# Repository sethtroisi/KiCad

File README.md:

# Seth Troisi's personal KiCad projects

## HomeLightsPCB

Used in Mourning Owl and Dream Willow

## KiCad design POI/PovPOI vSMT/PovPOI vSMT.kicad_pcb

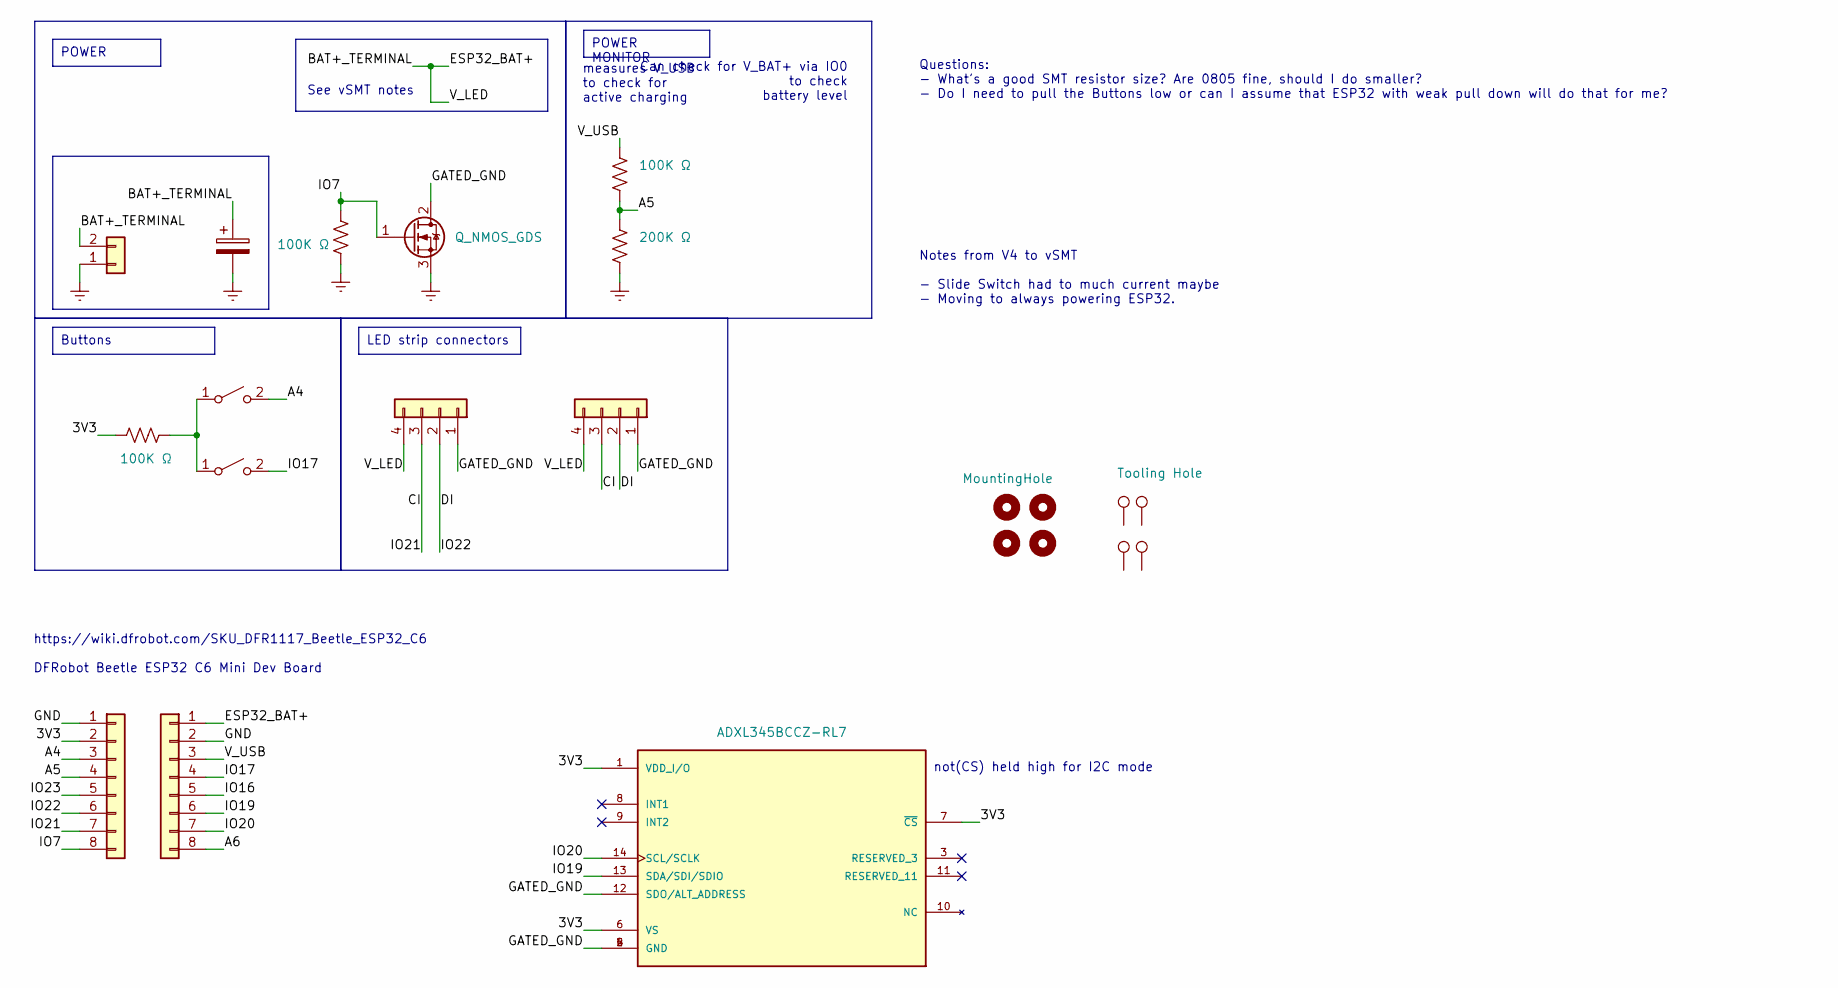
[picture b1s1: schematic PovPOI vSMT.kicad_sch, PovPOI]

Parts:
BatteryConn1: Conn_01x02; PinSocket_1x02_P2.54mm_Vertical
C2: C_Polarized; R_0805_2012Metric_Pad1.20x1.40mm_HandSolder; JLC 0805
H1, H2, H3, H4: MountingHole; MountingHole_2.2mm_M2_Pad
J2, J4: Conn_01x08; PinSocket_1x08_P2.54mm_Vertical
J3, J5: Conn_01x04; PinHeader_1x04_P2.54mm_Vertical_LARGER_HOLES
Q2: Q_NMOS_GDS; TO-252-2
R1, R5, R6: 100K Ω; R_0805_2012Metric_Pad1.20x1.40mm_HandSolder; LCSC C149504
R3: 200K Ω; R_0805_2012Metric_Pad1.20x1.40mm_HandSolder; LCSC C17539
SW1, SW2: SW_SPST; SW_SPST_EVQP7C; LCSC C388883
TP1, TP2, TP3, TP4: Tooling Hole; ToolingHole_JLCPCB
U2: ADXL345BCCZ-RL7; PQFN80P500X300X100-14N; PARTREV B; LCSC C9667

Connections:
/3V3: J2.2, R5.2, U2.1 (VDD_I/O), U2.6 (VS), U2.7 (~CS)
/A4: J2.3, SW2.2 (B)
/A5: J2.4, R1.1, R3.2
/A6: J4.8
/BAT+_TERMINAL: BatteryConn1.2, C2.1, J3.4, J4.1, J5.4
/CI: J2.7, J3.3, J5.3
/DI: J2.6, J3.2, J5.2
/GATED_GND: J3.1, J5.1, Q2.2 (D), U2.2 (GND), U2.4 (GND), U2.5 (GND), U2.12 (SDO/ALT_ADDRESS)
/IO7: J2.8, Q2.1 (G), R6.2
/IO16: J4.5
/IO17: J4.4, SW1.2 (B)
/IO19: J4.6, U2.13 (SDA/SDI/SDIO)
/IO20: J4.7, U2.14 (SCL/SCLK)
/IO23: J2.5
/V_USB: J4.3, R1.2
GND: BatteryConn1.1, C2.2, J2.1, J4.2, Q2.3 (S), R3.1, R6.1
unnamed: R5.1, SW1.1 (A), SW2.1 (A)

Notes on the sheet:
POWER
LED strip connectors
POWER MONITOR
Buttons
Notes from V4 to vSMT - Slide Switch had to much current maybe - Moving to always powering ESP32.
Can check for V_BAT+ via IO0 to check battery level
https://wiki.dfrobot.com/SKU_DFR1117_Beetle_ESP32_C6 DFRobot Beetle ESP32 C6 Mini Dev Board
Questions: - What's a good SMT resistor size? Are 0805 fine, should I do smaller? - Do I need to pull the Buttons low or can I assume that ESP32 with weak pull down will do that for me?
See vSMT notes
not(CS) held high for I2C mode
measures V_USB to check for active charging

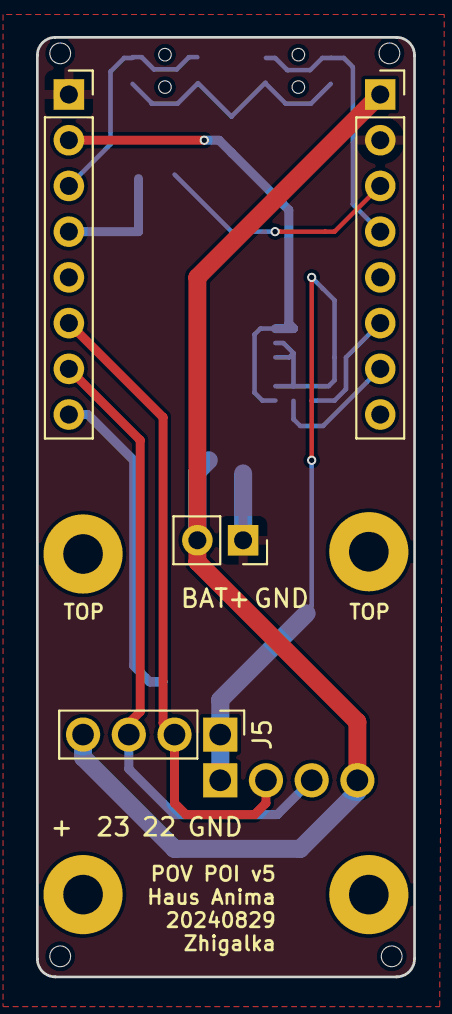
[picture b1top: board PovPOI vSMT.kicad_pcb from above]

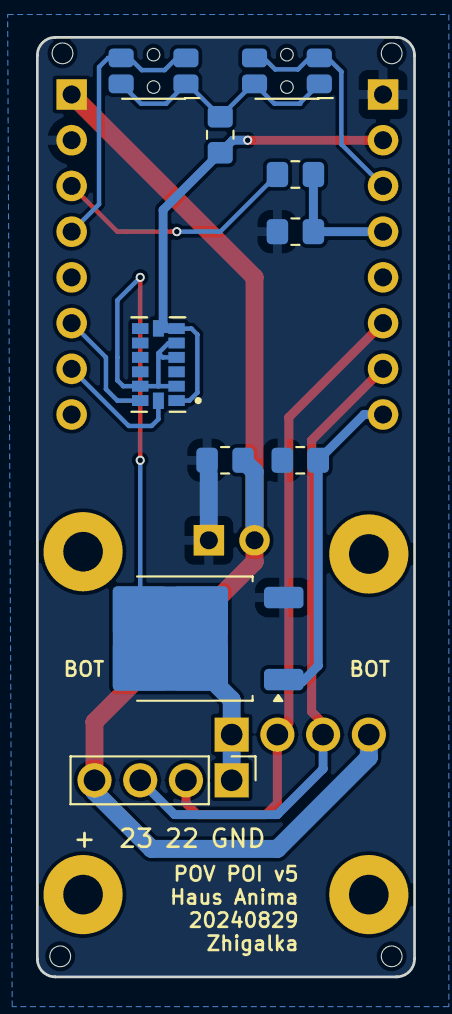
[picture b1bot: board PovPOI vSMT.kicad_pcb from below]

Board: 2 copper layers, 21.0 x 52.2 mm, 22 parts (10 on the bottom side), 14 nets.

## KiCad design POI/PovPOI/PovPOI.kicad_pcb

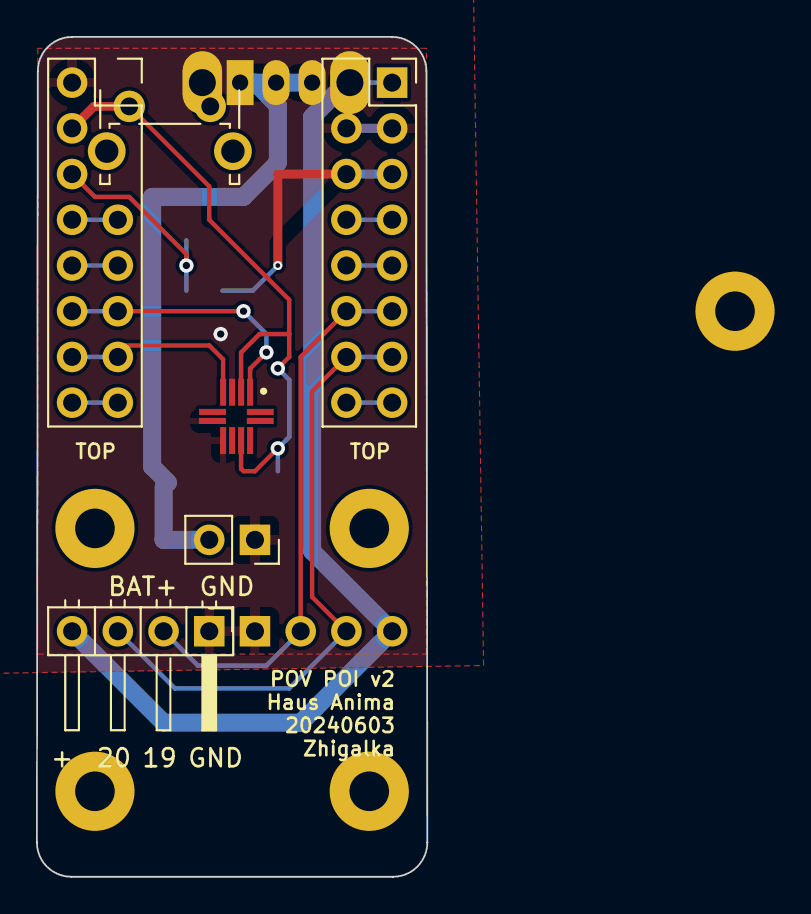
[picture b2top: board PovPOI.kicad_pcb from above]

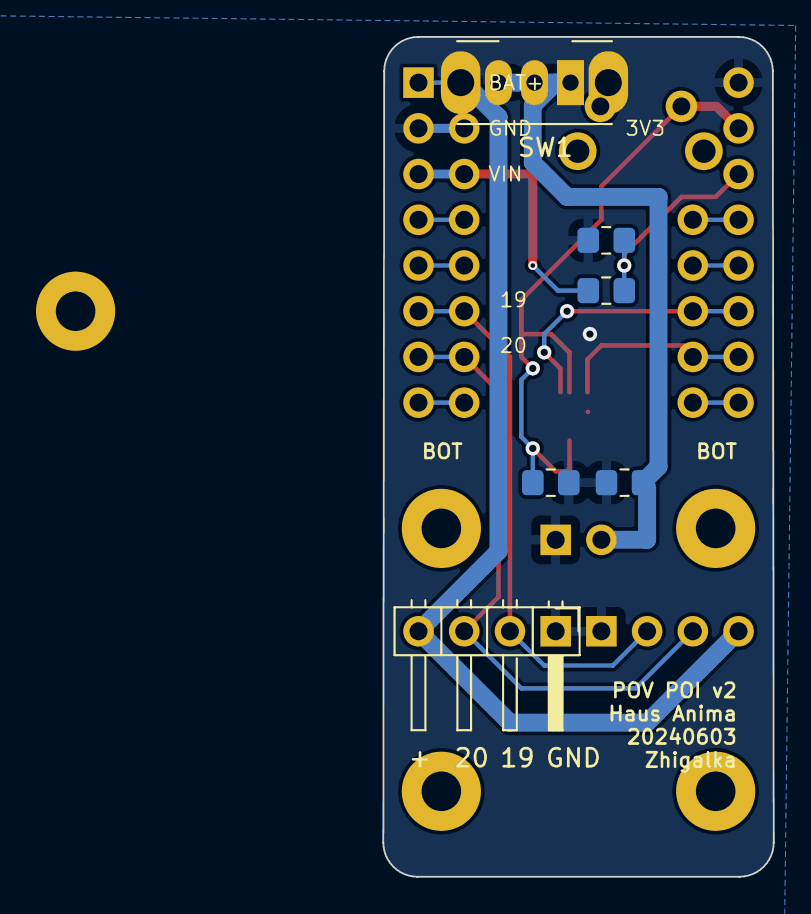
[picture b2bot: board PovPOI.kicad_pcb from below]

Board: 2 copper layers, 21.7 x 46.7 mm, 17 parts (6 on the bottom side), 16 nets.

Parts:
BatteryConn1: Conn_01x02; PinSocket_1x02_P2.54mm_Vertical
C1, C2: C_Polarized; R_0805_2012Metric_Pad1.20x1.40mm_HandSolder
H1, H2, H3, H4, H5: MountingHole; MountingHole_2.2mm_M2_Pad
J1, J2: Conn_02x08_Top_Bottom; PinSocket_2x08_P2.54mm_Vertical
J3, J5: Conn_01x04; PinHeader_1x04_P2.54mm_Horizontal_Seth
R1, R2: R_US; R_0805_2012Metric_Pad1.20x1.40mm_HandSolder
SW1: SW_SPDT; SW_Slide_SPDT_Angled_CK_OS102011MA1Q
SW2: SW_SPST; SW_Tactile_SPST_Angled_PTS645Vx39-2LFS
U1: MC3479; PQFN50P200X200X100-12N_HandSoldering

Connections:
/3V3: C1.1, J1.4, SW2.1 (A), U1.2 (~CS), U1.9 (VDD)
/5: J1.7, J1.8
/6: J2.15, J2.16
/7: J1.15, J1.16
/16: J2.9, J2.10
/17: J2.7, J2.8, SW2.2 (B)
/19: J2.11, J2.12, J3.2, J5.2
/20: J2.13, J2.14, J3.3, J5.3
/23: J1.9, J1.10
/BAT_TERMINAL: BatteryConn1.2, C2.1, SW1.1 (A), SW1.2 (B)
/CHIP_BAT+: J2.1, J3.4, J5.4, SW1.3 (C)
/IO4: J1.6, R1.1, R2.2
/IO21: J1.13, J1.14, U1.4 (DIN_SDA)
/IO22: J1.11, J1.12, U1.1 (SCK_SCL)
/VIN: J2.5, J2.6, R1.2
GND: BatteryConn1.1, C1.2, C2.2, J1.2, J2.3, J2.4, J3.1, J5.1, R2.1, U1.3 (DOUT_A6), U1.6 (GND), U1.7 (VPP)

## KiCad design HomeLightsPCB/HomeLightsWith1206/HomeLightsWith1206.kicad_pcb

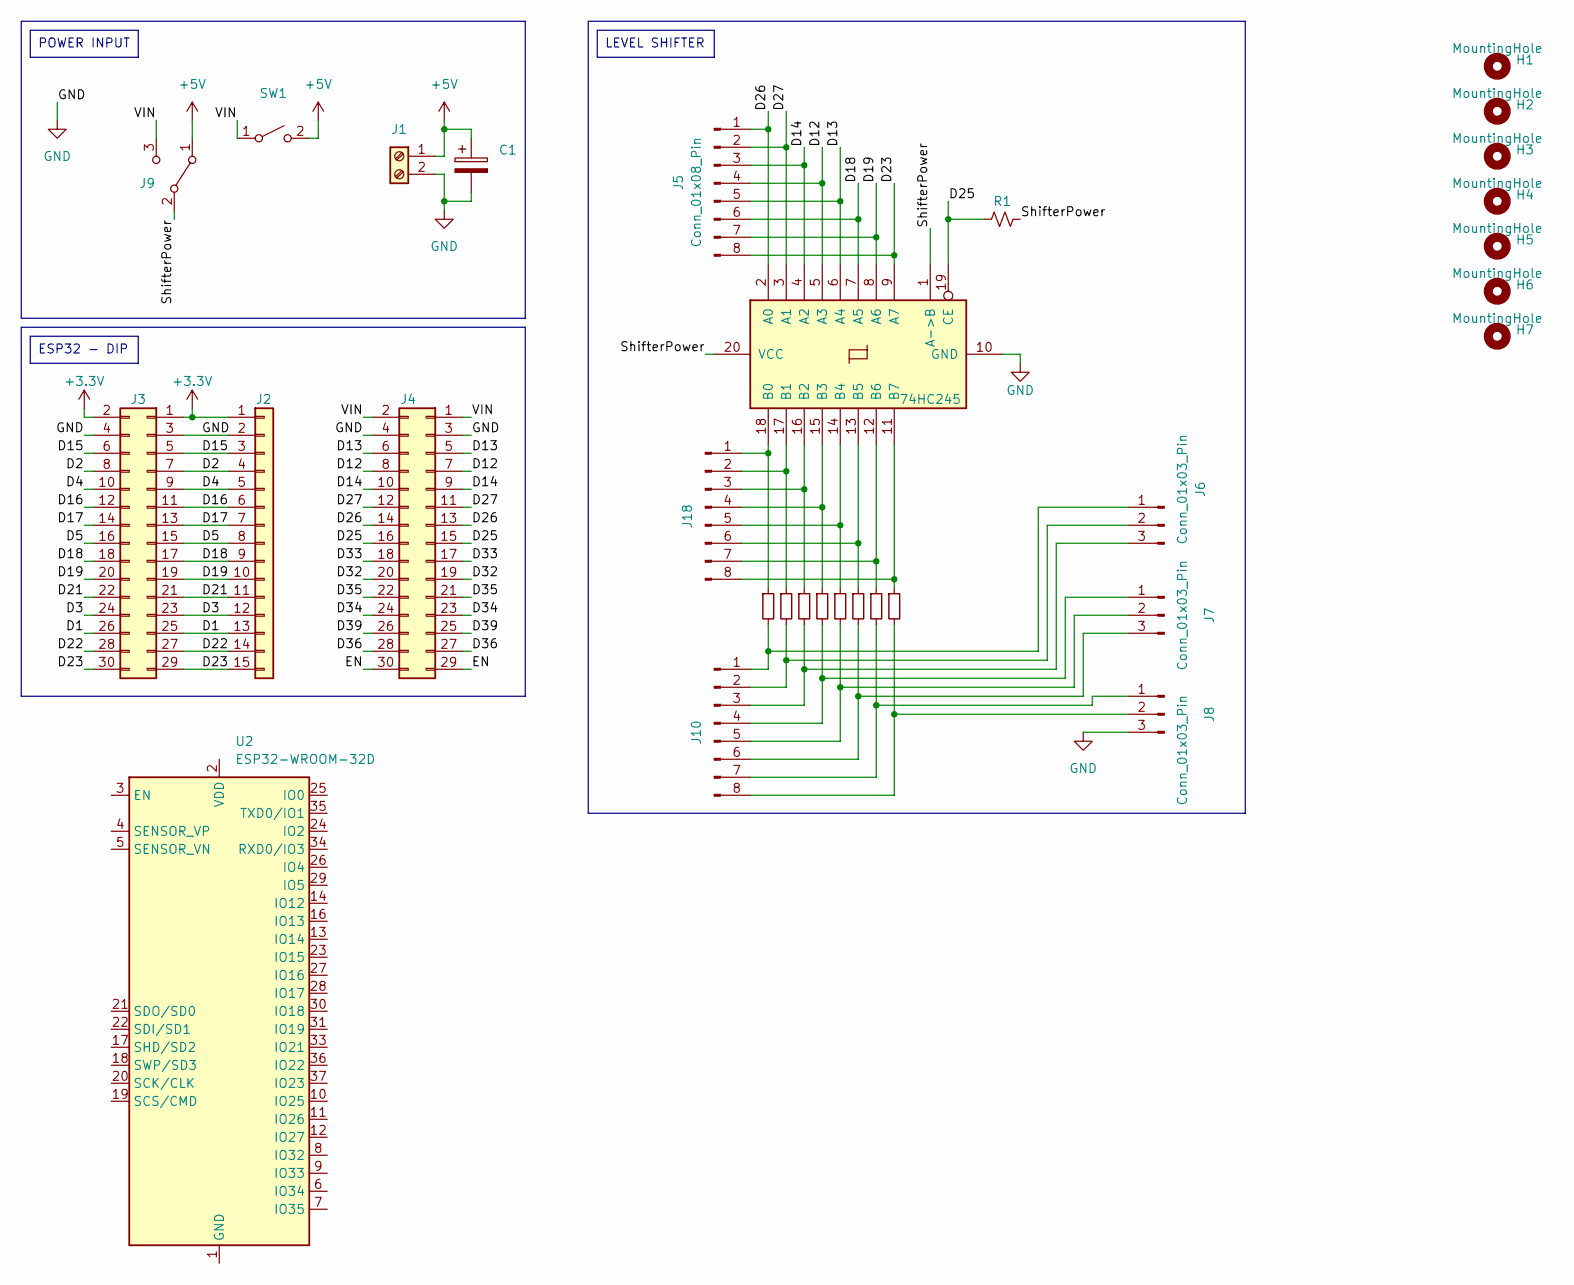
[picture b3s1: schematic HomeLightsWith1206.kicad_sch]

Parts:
C1: C_Polarized; CP_Radial_D4.0mm_P2.00mm
H1, H2, H3, H4, H5, H6: MountingHole; MountingHole_2.2mm_M2_DIN965_Pad
H7: MountingHole; MountingHole_3.2mm_M3
J1: Conn_01x02_Pin; TerminalBlock_Phoenix_MKDS-1,5-2-5.08_1x02_P5.08mm_Horizont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
J2: Conn_01x15; PinHeader_1x15_P2.54mm_Vertical
J3, J4: Conn_02x15_Odd_Even; PinSocket_2x15_P2.54mm_Vertical
J5, J10, J18: Conn_01x08_Pin; PinHeader_1x08_P2.54mm_Vertical
J6, J7: Conn_01x03_Pin; JST_VH_B3P-VH_1x03_P3.96mm_Vertical
J8: Conn_01x03_Pin; JST_VH_B3P-VH-B_1x03_P3.96mm_Vertical
J9: Conn_01x03_Pin; PinSocket_1x03_P2.54mm_Vertical
R1: R_Small_US; R_Axial_DIN0207_L6.3mm_D2.5mm_P10.16mm_Horizontal
R2, R3, R4, R5, R6, R7, R8, R9: R_Small; R_1206_3216Metric_Pad1.30x1.75mm_HandSolder
SW1: SW_SPST; PinSocket_1x02_P2.54mm_Vertical
U1: 74HC245; DIP-20_W7.62mm
U2: ESP32-WROOM-32D; DIP-30_W25.4mm

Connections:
+3.3V: J2.1, J3.1, J3.2
+5V: C1.1, J1.1, J9.1 (A), SW1.2 (B)
/D1: J2.13, J3.25, J3.26
/D2: J2.4, J3.7, J3.8
/D3: J2.12, J3.23, J3.24
/D4: J2.5, J3.9, J3.10
/D5: J2.8, J3.15, J3.16
/D12: J4.7, J4.8, J5.4, U1.5 (A3)
/D13: J4.5, J4.6, J5.5, U1.6 (A4)
/D14: J4.9, J4.10, J5.3, U1.4 (A2)
/D15: J2.3, J3.5, J3.6
/D16: J2.6, J3.11, J3.12
/D17: J2.7, J3.13, J3.14
/D18: J2.9, J3.17, J3.18, J5.6, U1.7 (A5)
/D19: J2.10, J3.19, J3.20, J5.7, U1.8 (A6)
/D21: J2.11, J3.21, J3.22
/D22: J2.14, J3.27, J3.28
/D23: J2.15, J3.29, J3.30, J5.8, U1.9 (A7)
/D25: J4.15, J4.16, R1.1, U1.19 (CE)
/D26: J4.13, J4.14, J5.1, U1.2 (A0)
/D27: J4.11, J4.12, J5.2, U1.3 (A1)
/D32: J4.19, J4.20
/D33: J4.17, J4.18
/D34: J4.23, J4.24
/D35: J4.21, J4.22
/D36: J4.27, J4.28
/D39: J4.25, J4.26
/EN: J4.29, J4.30
/ShifterPower: J9.2 (B), R1.2, U1.1 (A->B), U1.20 (VCC)
/VIN: J4.1, J4.2, J9.3 (C), SW1.1 (A)
GND: C1.2, J1.2, J2.2, J3.3, J3.4, J4.3, J4.4, J8.3, U1.10 (GND)
unnamed: J6.1, J10.1, R2.2
unnamed: J6.2, J10.2, R3.2
unnamed: J6.3, J10.3, R4.2
unnamed: J7.1, J10.4, R5.2
unnamed: J7.2, J10.5, R6.2
unnamed: J7.3, J10.6, R7.2
unnamed: J8.1, J10.7, R8.2
unnamed: J8.2, J10.8, R9.2
unnamed: J18.1, R2.1, U1.18 (B0)
unnamed: J18.2, R3.1, U1.17 (B1)
unnamed: J18.3, R4.1, U1.16 (B2)
unnamed: J18.4, R5.1, U1.15 (B3)
unnamed: J18.5, R6.1, U1.14 (B4)
unnamed: J18.6, R7.1, U1.13 (B5)
unnamed: J18.7, R8.1, U1.12 (B6)
unnamed: J18.8, R9.1, U1.11 (B7)
unnamed: U2.1 (GND), U2.15 (GND), U2.38 (GND), U2.39 (GND)

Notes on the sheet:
POWER INPUT
ESP32 - DIP
LEVEL SHIFTER

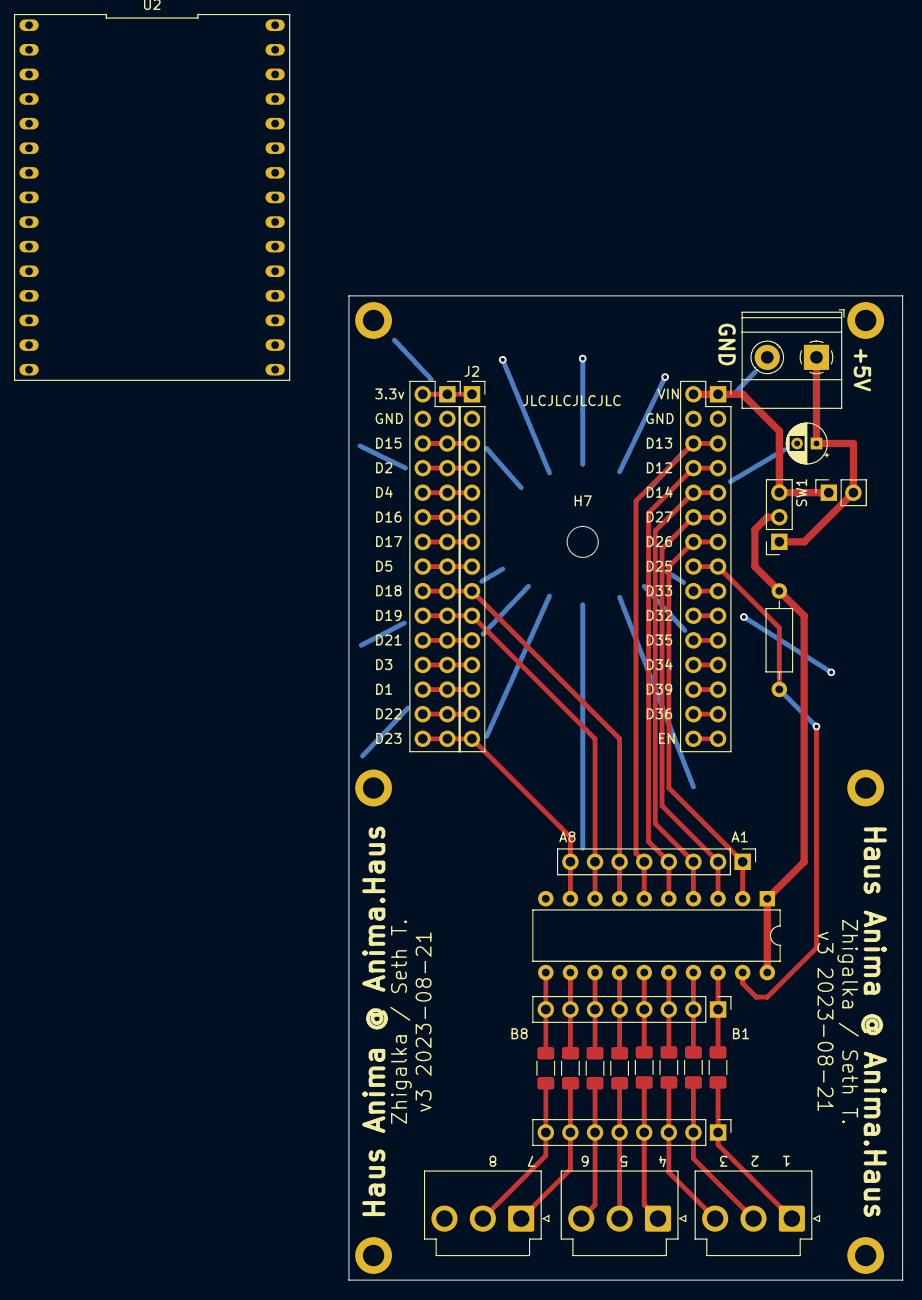
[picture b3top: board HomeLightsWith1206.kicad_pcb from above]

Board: 2 copper layers, 57.2 x 101.6 mm, 31 parts (0 on the bottom side), 48 nets.

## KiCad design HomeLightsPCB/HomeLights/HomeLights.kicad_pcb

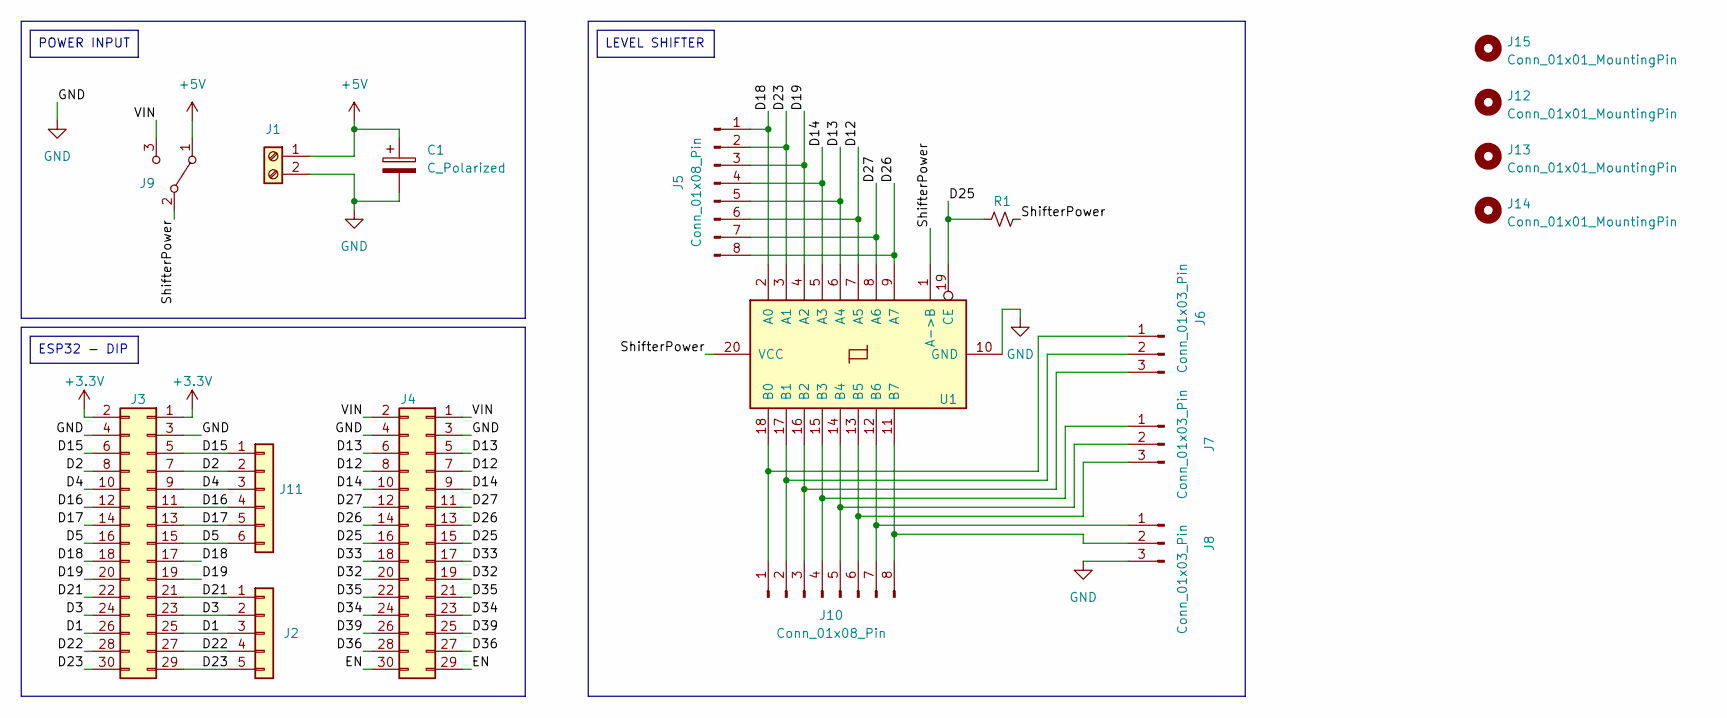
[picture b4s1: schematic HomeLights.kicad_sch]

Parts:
C1: C_Polarized; CP_Radial_D4.0mm_P2.00mm
J1: Conn_01x02_Pin; TerminalBlock_Phoenix_MKDS-1,5-2-5.08_1x02_P5.08mm_Horizont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
J2: Conn_01x05_Pin; PinHeader_1x05_P2.54mm_Vertical
J3, J4: Conn_02x15_Odd_Even; PinSocket_2x15_P2.54mm_Vertical
J5, J10: Conn_01x08_Pin; PinHeader_1x08_P2.54mm_Vertical
J6, J7: Conn_01x03_Pin; JST_VH_B3P-VH_1x03_P3.96mm_Vertical
J8: Conn_01x03_Pin; JST_VH_B3P-VH-B_1x03_P3.96mm_Vertical
J9: Conn_01x03_Pin; PinSocket_1x03_P2.54mm_Vertical
J11: Conn_01x06_Pin; PinHeader_1x06_P2.54mm_Vertical
J12, J13, J14, J15: Conn_01x01_MountingPin; MountingHole_2.2mm_M2_DIN965_Pad
R1: R_Small_US; R_Axial_DIN0207_L6.3mm_D2.5mm_P10.16mm_Horizontal
U1: 74HC245; DIP-20_W7.62mm

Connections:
+3.3V: J3.1, J3.2
+5V: C1.1, J1.1, J9.1 (A)
/D1: J2.3, J3.25, J3.26
/D2: J3.7, J3.8, J11.2
/D3: J2.2, J3.23, J3.24
/D4: J3.9, J3.10, J11.3
/D5: J3.15, J3.16, J11.6
/D12: J4.7, J4.8, J5.6, U1.7 (A5)
/D13: J4.5, J4.6, J5.5, U1.6 (A4)
/D14: J4.9, J4.10, J5.4, U1.5 (A3)
/D15: J3.5, J3.6, J11.1
/D16: J3.11, J3.12, J11.4
/D17: J3.13, J3.14, J11.5
/D18: J3.17, J3.18, J5.1, U1.2 (A0)
/D19: J3.19, J3.20, J5.3, U1.4 (A2)
/D21: J2.1, J3.21, J3.22
/D22: J2.4, J3.27, J3.28
/D23: J2.5, J3.29, J3.30, J5.2, U1.3 (A1)
/D25: J4.15, J4.16, R1.1, U1.19 (CE)
/D26: J4.13, J4.14, J5.8, U1.9 (A7)
/D27: J4.11, J4.12, J5.7, U1.8 (A6)
/D32: J4.19, J4.20
/D33: J4.17, J4.18
/D34: J4.23, J4.24
/D35: J4.21, J4.22
/D36: J4.27, J4.28
/D39: J4.25, J4.26
/EN: J4.29, J4.30
/ShifterPower: J9.2 (B), R1.2, U1.1 (A->B), U1.20 (VCC)
/VIN: J4.1, J4.2, J9.3 (C)
GND: C1.2, J1.2, J3.3, J3.4, J4.3, J4.4, J8.3, U1.10 (GND)
unnamed: J6.1, J10.1, U1.18 (B0)
unnamed: J6.2, J10.2, U1.17 (B1)
unnamed: J6.3, J10.3, U1.16 (B2)
unnamed: J7.1, J10.4, U1.15 (B3)
unnamed: J7.2, J10.5, U1.14 (B4)
unnamed: J7.3, J10.6, U1.13 (B5)
unnamed: J8.1, J10.7, U1.12 (B6)
unnamed: J8.2, J10.8, U1.11 (B7)

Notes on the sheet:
POWER INPUT
ESP32 - DIP
LEVEL SHIFTER

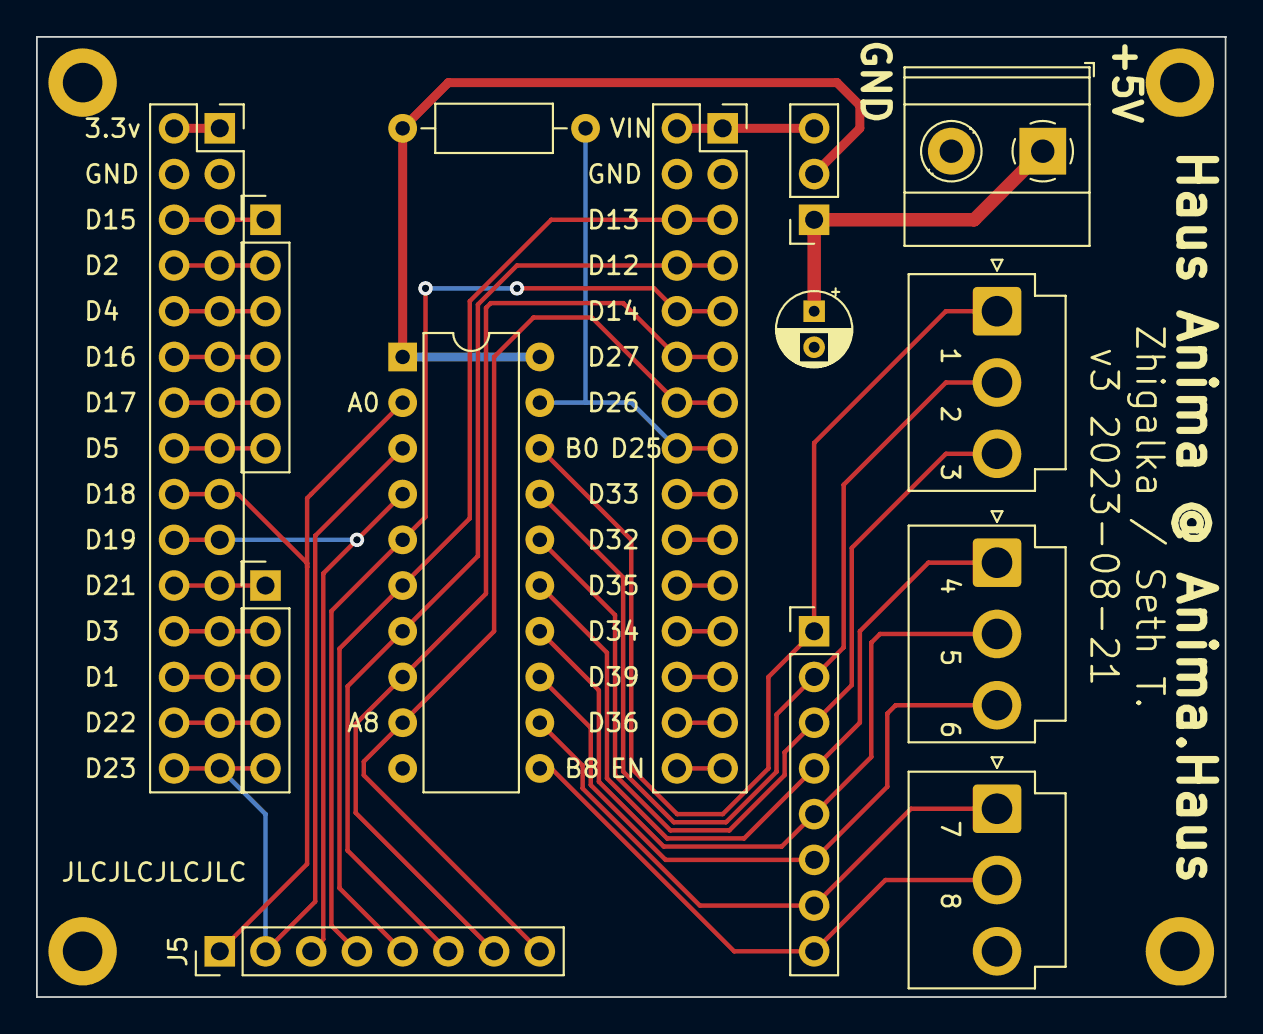
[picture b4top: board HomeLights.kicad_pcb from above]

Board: 2 copper layers, 66.0 x 53.3 mm, 18 parts (0 on the bottom side), 39 nets.

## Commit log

2023-10-18 Initial commit to KiCad
2023-10-18 Add GPLv3 LICENSE
2023-10-18 HomeLightsPCB
2024-03-30 Historical versions of PovPOI
2024-03-30 Added PovPOI project
2024-06-06 POV POI v2, working towards v3
2024-08-16 POV POI v2.5 before accel import
2024-09-05 New library files
2024-09-05 Unknown changes in PovPOI
2024-09-05 PovPOi v2.5 and vSMT
2024-09-05 Removed v2.5 attempt #1 to add accelerometer to DFRobot ESP32
2024-09-05 Ignore fp-info-cache files
2024-09-05 Reloaded PovPOI vSMT from worklaptop
